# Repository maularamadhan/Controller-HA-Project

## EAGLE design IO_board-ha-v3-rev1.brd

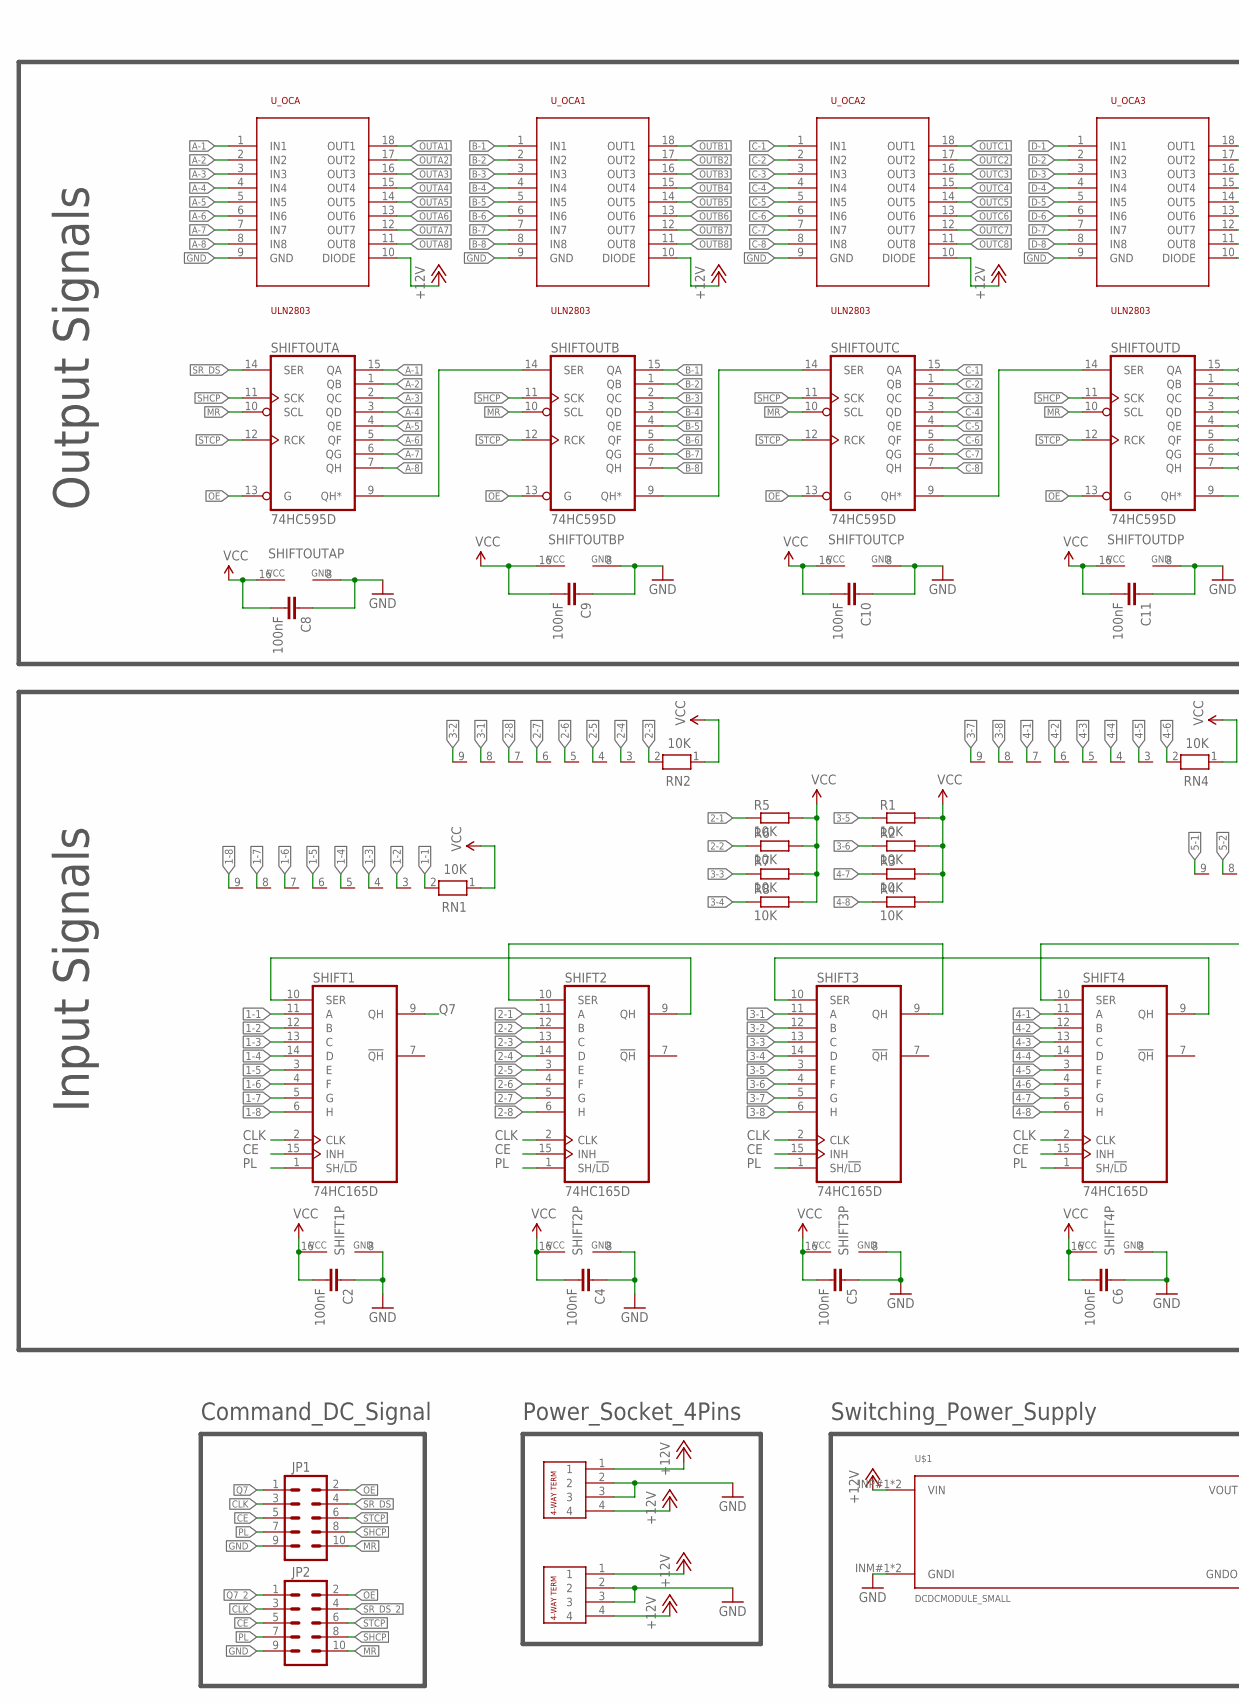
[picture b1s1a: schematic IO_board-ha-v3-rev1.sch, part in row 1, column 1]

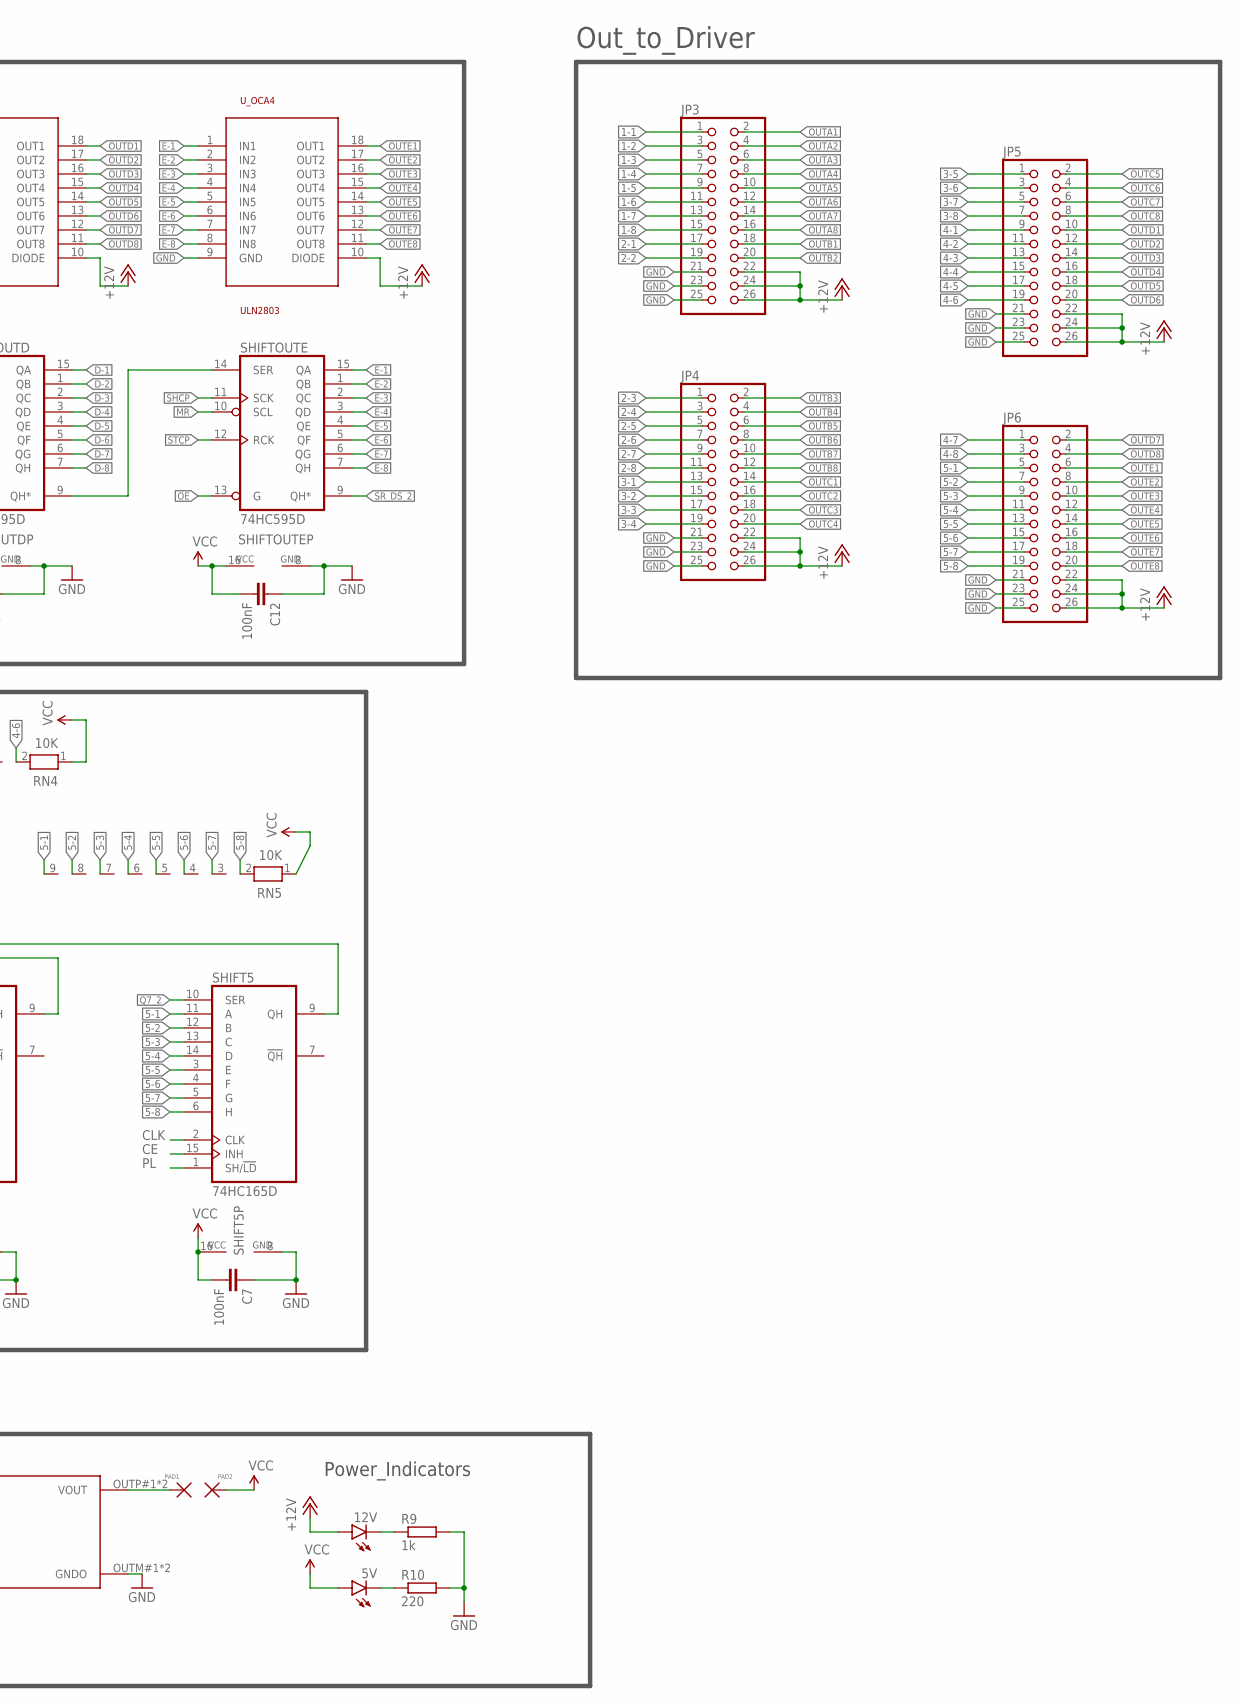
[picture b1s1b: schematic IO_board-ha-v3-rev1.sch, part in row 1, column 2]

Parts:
5V, 12V: LED3MM
C2, C4, C5, C6, C7, C8, C9, C10, C11, C12: 100nF; C0603K
J1, J2: 4-PIN-CON-1759017
JP1, JP2: M05X2SHD; 2X5-SHROUDED
JP3, JP4, JP5, JP6: PINHD-2X13; 2X13
R1, R2, R3, R4, R5, R6, R7, R8: 10K; R0603
R9: 1k; R0805
R10: 220; R0805
RN1, RN2, RN4, RN5: 10K; RN-9
SHIFT1, SHIFT2, SHIFT3, SHIFT4, SHIFT5: 74HC165D; SO16
SHIFTOUTA: 74HC595D; SO16
SHIFTOUTB: 74HC595D; SO16
SHIFTOUTC: 74HC595D; SO16
SHIFTOUTD: 74HC595D; SO16
SHIFTOUTE: 74HC595D; SO16
U$1: DCDCMODULE_SMALL; DCDCMODULE-SMALL
U$2: DOUBLE_SMALL_PAD
U_OCA, U_OCA1, U_OCA2, U_OCA3, U_OCA4: ULN2803; SO18L

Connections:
1-1: JP3.1, RN1.2, SHIFT1.11 (A)
1-2: JP3.3, RN1.3, SHIFT1.12 (B)
1-3: JP3.5, RN1.4, SHIFT1.13 (C)
1-4: JP3.7, RN1.5, SHIFT1.14 (D)
1-5: JP3.9, RN1.6, SHIFT1.3 (E)
1-6: JP3.11, RN1.7, SHIFT1.4 (F)
1-7: JP3.13, RN1.8, SHIFT1.5 (G)
1-8: JP3.15, RN1.9, SHIFT1.6 (H)
2-1: JP3.17, R5.1, SHIFT2.11 (A)
2-2: JP3.19, R6.1, SHIFT2.12 (B)
2-3: JP4.1, RN2.2, SHIFT2.13 (C)
2-4: JP4.3, RN2.3, SHIFT2.14 (D)
2-5: JP4.5, RN2.4, SHIFT2.3 (E)
2-6: JP4.7, RN2.5, SHIFT2.4 (F)
2-7: JP4.9, RN2.6, SHIFT2.5 (G)
2-8: JP4.11, RN2.7, SHIFT2.6 (H)
3-1: JP4.13, RN2.8, SHIFT3.11 (A)
3-2: JP4.15, RN2.9, SHIFT3.12 (B)
3-3: JP4.17, R7.1, SHIFT3.13 (C)
3-4: JP4.19, R8.1, SHIFT3.14 (D)
3-5: JP5.1, R1.1, SHIFT3.3 (E)
3-6: JP5.3, R2.1, SHIFT3.4 (F)
3-7: JP5.5, RN4.9, SHIFT3.5 (G)
3-8: JP5.7, RN4.8, SHIFT3.6 (H)
4-1: JP5.9, RN4.7, SHIFT4.11 (A)
4-2: JP5.11, RN4.6, SHIFT4.12 (B)
4-3: JP5.13, RN4.5, SHIFT4.13 (C)
4-4: JP5.15, RN4.4, SHIFT4.14 (D)
4-5: JP5.17, RN4.3, SHIFT4.3 (E)
4-6: JP5.19, RN4.2, SHIFT4.4 (F)
4-7: JP6.1, R3.1, SHIFT4.5 (G)
4-8: JP6.3, R4.1, SHIFT4.6 (H)
5-1: JP6.5, RN5.9, SHIFT5.11 (A)
5-2: JP6.7, RN5.8, SHIFT5.12 (B)
5-3: JP6.9, RN5.7, SHIFT5.13 (C)
5-4: JP6.11, RN5.6, SHIFT5.14 (D)
5-5: JP6.13, RN5.5, SHIFT5.3 (E)
5-6: JP6.15, RN5.4, SHIFT5.4 (F)
5-7: JP6.17, RN5.3, SHIFT5.5 (G)
5-8: JP6.19, RN5.2, SHIFT5.6 (H)
+12V: 12V.A, J1.1, J1.4, J2.1, J2.4, JP3.22, JP3.24, JP3.26, JP4.22, JP4.24, JP4.26, JP5.22, JP5.24, JP5.26, JP6.22, JP6.24, JP6.26, U$1.INP#1 (VIN), U$1.INP#2 (VIN), U_OCA.10 (DIODE), U_OCA1.10 (DIODE), U_OCA2.10 (DIODE), U_OCA3.10 (DIODE), U_OCA4.10 (DIODE)
A-1: SHIFTOUTA.15 (QA), U_OCA.1 (IN1)
A-2: SHIFTOUTA.1 (QB), U_OCA.2 (IN2)
A-3: SHIFTOUTA.2 (QC), U_OCA.3 (IN3)
A-4: SHIFTOUTA.3 (QD), U_OCA.4 (IN4)
A-5: SHIFTOUTA.4 (QE), U_OCA.5 (IN5)
A-6: SHIFTOUTA.5 (QF), U_OCA.6 (IN6)
A-7: SHIFTOUTA.6 (QG), U_OCA.7 (IN7)
A-8: SHIFTOUTA.7 (QH), U_OCA.8 (IN8)
B-1: SHIFTOUTB.15 (QA), U_OCA1.1 (IN1)
B-2: SHIFTOUTB.1 (QB), U_OCA1.2 (IN2)
B-3: SHIFTOUTB.2 (QC), U_OCA1.3 (IN3)
B-4: SHIFTOUTB.3 (QD), U_OCA1.4 (IN4)
B-5: SHIFTOUTB.4 (QE), U_OCA1.5 (IN5)
B-6: SHIFTOUTB.5 (QF), U_OCA1.6 (IN6)
B-7: SHIFTOUTB.6 (QG), U_OCA1.7 (IN7)
B-8: SHIFTOUTB.7 (QH), U_OCA1.8 (IN8)
C-1: SHIFTOUTC.15 (QA), U_OCA2.1 (IN1)
C-2: SHIFTOUTC.1 (QB), U_OCA2.2 (IN2)
C-3: SHIFTOUTC.2 (QC), U_OCA2.3 (IN3)
C-4: SHIFTOUTC.3 (QD), U_OCA2.4 (IN4)
C-5: SHIFTOUTC.4 (QE), U_OCA2.5 (IN5)
C-6: SHIFTOUTC.5 (QF), U_OCA2.6 (IN6)
C-7: SHIFTOUTC.6 (QG), U_OCA2.7 (IN7)
C-8: SHIFTOUTC.7 (QH), U_OCA2.8 (IN8)
CE: JP1.5, JP2.5, SHIFT1.15 (INH), SHIFT2.15 (INH), SHIFT3.15 (INH), SHIFT4.15 (INH), SHIFT5.15 (INH)
CLK: JP1.3, JP2.3, SHIFT1.2 (CLK), SHIFT2.2 (CLK), SHIFT3.2 (CLK), SHIFT4.2 (CLK), SHIFT5.2 (CLK)
D-1: SHIFTOUTD.15 (QA), U_OCA3.1 (IN1)
D-2: SHIFTOUTD.1 (QB), U_OCA3.2 (IN2)
D-3: SHIFTOUTD.2 (QC), U_OCA3.3 (IN3)
D-4: SHIFTOUTD.3 (QD), U_OCA3.4 (IN4)
D-5: SHIFTOUTD.4 (QE), U_OCA3.5 (IN5)
D-6: SHIFTOUTD.5 (QF), U_OCA3.6 (IN6)
D-7: SHIFTOUTD.6 (QG), U_OCA3.7 (IN7)
D-8: SHIFTOUTD.7 (QH), U_OCA3.8 (IN8)
E-1: SHIFTOUTE.15 (QA), U_OCA4.1 (IN1)
E-2: SHIFTOUTE.1 (QB), U_OCA4.2 (IN2)
E-3: SHIFTOUTE.2 (QC), U_OCA4.3 (IN3)
E-4: SHIFTOUTE.3 (QD), U_OCA4.4 (IN4)
E-5: SHIFTOUTE.4 (QE), U_OCA4.5 (IN5)
E-6: SHIFTOUTE.5 (QF), U_OCA4.6 (IN6)
E-7: SHIFTOUTE.6 (QG), U_OCA4.7 (IN7)
E-8: SHIFTOUTE.7 (QH), U_OCA4.8 (IN8)
GND: C2.1, C4.1, C5.1, C6.1, C7.1, C8.1, C9.1, C10.1, C11.1, C12.1, J1.2, J1.3, J2.2, J2.3, JP1.9, JP2.9, JP3.21, JP3.23, JP3.25, JP4.21, JP4.23, JP4.25, JP5.21, JP5.23, JP5.25, JP6.21, JP6.23, JP6.25, R9.2, R10.2, SHIFT1.8 (GND), SHIFT2.8 (GND), SHIFT3.8 (GND), SHIFT4.8 (GND), SHIFT5.8 (GND), SHIFTOUTA.8 (GND), SHIFTOUTB.8 (GND), SHIFTOUTC.8 (GND), SHIFTOUTD.8 (GND), SHIFTOUTE.8 (GND), U$1.INM#1 (GNDI), U$1.INM#2 (GNDI), U$1.OUTM#1 (GNDO), U$1.OUTM#2 (GNDO), U_OCA.9 (GND), U_OCA1.9 (GND), U_OCA2.9 (GND), U_OCA3.9 (GND), U_OCA4.9 (GND)
MR: JP1.10, JP2.10, SHIFTOUTA.10 (SCL), SHIFTOUTB.10 (SCL), SHIFTOUTC.10 (SCL), SHIFTOUTD.10 (SCL), SHIFTOUTE.10 (SCL)
unnamed: U$1.OUTP#1 (VOUT), U$1.OUTP#2 (VOUT), U$2.PAD1
unnamed: 12V.K (C), R9.1
unnamed: 5V.K (C), R10.1
unnamed: SHIFT2.10 (SER), SHIFT3.9 (QH)
unnamed: SHIFT3.10 (SER), SHIFT4.9 (QH)
unnamed: SHIFT4.10 (SER), SHIFT5.9 (QH)
unnamed: SHIFTOUTA.9 (QH*), SHIFTOUTB.14 (SER)
unnamed: SHIFTOUTC.9 (QH*), SHIFTOUTD.14 (SER)
unnamed: SHIFTOUTB.9 (QH*), SHIFTOUTC.14 (SER)
unnamed: SHIFTOUTD.9 (QH*), SHIFTOUTE.14 (SER)
unnamed: SHIFT1.10 (SER), SHIFT2.9 (QH)
OE: JP1.2, JP2.2, SHIFTOUTA.13 (G), SHIFTOUTB.13 (G), SHIFTOUTC.13 (G), SHIFTOUTD.13 (G), SHIFTOUTE.13 (G)
OUTA1: JP3.2, U_OCA.18 (OUT1)
OUTA2: JP3.4, U_OCA.17 (OUT2)
OUTA3: JP3.6, U_OCA.16 (OUT3)
OUTA4: JP3.8, U_OCA.15 (OUT4)
OUTA5: JP3.10, U_OCA.14 (OUT5)
OUTA6: JP3.12, U_OCA.13 (OUT6)
OUTA7: JP3.14, U_OCA.12 (OUT7)
OUTA8: JP3.16, U_OCA.11 (OUT8)
OUTB1: JP3.18, U_OCA1.18 (OUT1)
OUTB2: JP3.20, U_OCA1.17 (OUT2)
OUTB3: JP4.2, U_OCA1.16 (OUT3)
OUTB4: JP4.4, U_OCA1.15 (OUT4)
OUTB5: JP4.6, U_OCA1.14 (OUT5)
OUTB6: JP4.8, U_OCA1.13 (OUT6)
OUTB7: JP4.10, U_OCA1.12 (OUT7)
OUTB8: JP4.12, U_OCA1.11 (OUT8)
OUTC1: JP4.14, U_OCA2.18 (OUT1)
OUTC2: JP4.16, U_OCA2.17 (OUT2)
OUTC3: JP4.18, U_OCA2.16 (OUT3)
OUTC4: JP4.20, U_OCA2.15 (OUT4)
OUTC5: JP5.2, U_OCA2.14 (OUT5)
OUTC6: JP5.4, U_OCA2.13 (OUT6)
OUTC7: JP5.6, U_OCA2.12 (OUT7)
OUTC8: JP5.8, U_OCA2.11 (OUT8)
OUTD1: JP5.10, U_OCA3.18 (OUT1)
OUTD2: JP5.12, U_OCA3.17 (OUT2)
OUTD3: JP5.14, U_OCA3.16 (OUT3)
OUTD4: JP5.16, U_OCA3.15 (OUT4)
OUTD5: JP5.18, U_OCA3.14 (OUT5)
OUTD6: JP5.20, U_OCA3.13 (OUT6)
OUTD7: JP6.2, U_OCA3.12 (OUT7)
OUTD8: JP6.4, U_OCA3.11 (OUT8)
OUTE1: JP6.6, U_OCA4.18 (OUT1)
OUTE2: JP6.8, U_OCA4.17 (OUT2)
OUTE3: JP6.10, U_OCA4.16 (OUT3)
OUTE4: JP6.12, U_OCA4.15 (OUT4)
OUTE5: JP6.14, U_OCA4.14 (OUT5)
OUTE6: JP6.16, U_OCA4.13 (OUT6)
OUTE7: JP6.18, U_OCA4.12 (OUT7)
OUTE8: JP6.20, U_OCA4.11 (OUT8)
PL: JP1.7, JP2.7, SHIFT1.1 (SH/!LD), SHIFT2.1 (SH/!LD), SHIFT3.1 (SH/!LD), SHIFT4.1 (SH/!LD), SHIFT5.1 (SH/!LD)
Q7: JP1.1, SHIFT1.9 (QH)
Q7_2: JP2.1, SHIFT5.10 (SER)
SHCP: JP1.8, JP2.8, SHIFTOUTA.11 (SCK), SHIFTOUTB.11 (SCK), SHIFTOUTC.11 (SCK), SHIFTOUTD.11 (SCK), SHIFTOUTE.11 (SCK)
SR_DS: JP1.4, SHIFTOUTA.14 (SER)
SR_DS_2: JP2.4, SHIFTOUTE.9 (QH*)
STCP: JP1.6, JP2.6, SHIFTOUTA.12 (RCK), SHIFTOUTB.12 (RCK), SHIFTOUTC.12 (RCK), SHIFTOUTD.12 (RCK), SHIFTOUTE.12 (RCK)
VCC: 5V.A, C2.2, C4.2, C5.2, C6.2, C7.2, C8.2, C9.2, C10.2, C11.2, C12.2, R1.2, R2.2, R3.2, R4.2, R5.2, R6.2, R7.2, R8.2, RN1.1, RN2.1, RN4.1, RN5.1, SHIFT1.16 (VCC), SHIFT2.16 (VCC), SHIFT3.16 (VCC), SHIFT4.16 (VCC), SHIFT5.16 (VCC), SHIFTOUTA.16 (VCC), SHIFTOUTB.16 (VCC), SHIFTOUTC.16 (VCC), SHIFTOUTD.16 (VCC), SHIFTOUTE.16 (VCC), U$2.PAD2

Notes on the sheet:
Input Signals
Output Signals
Out_to_Driver
Command_DC_Signal
Power_Socket_4Pins
Switching_Power_Supply
Power_Indicators

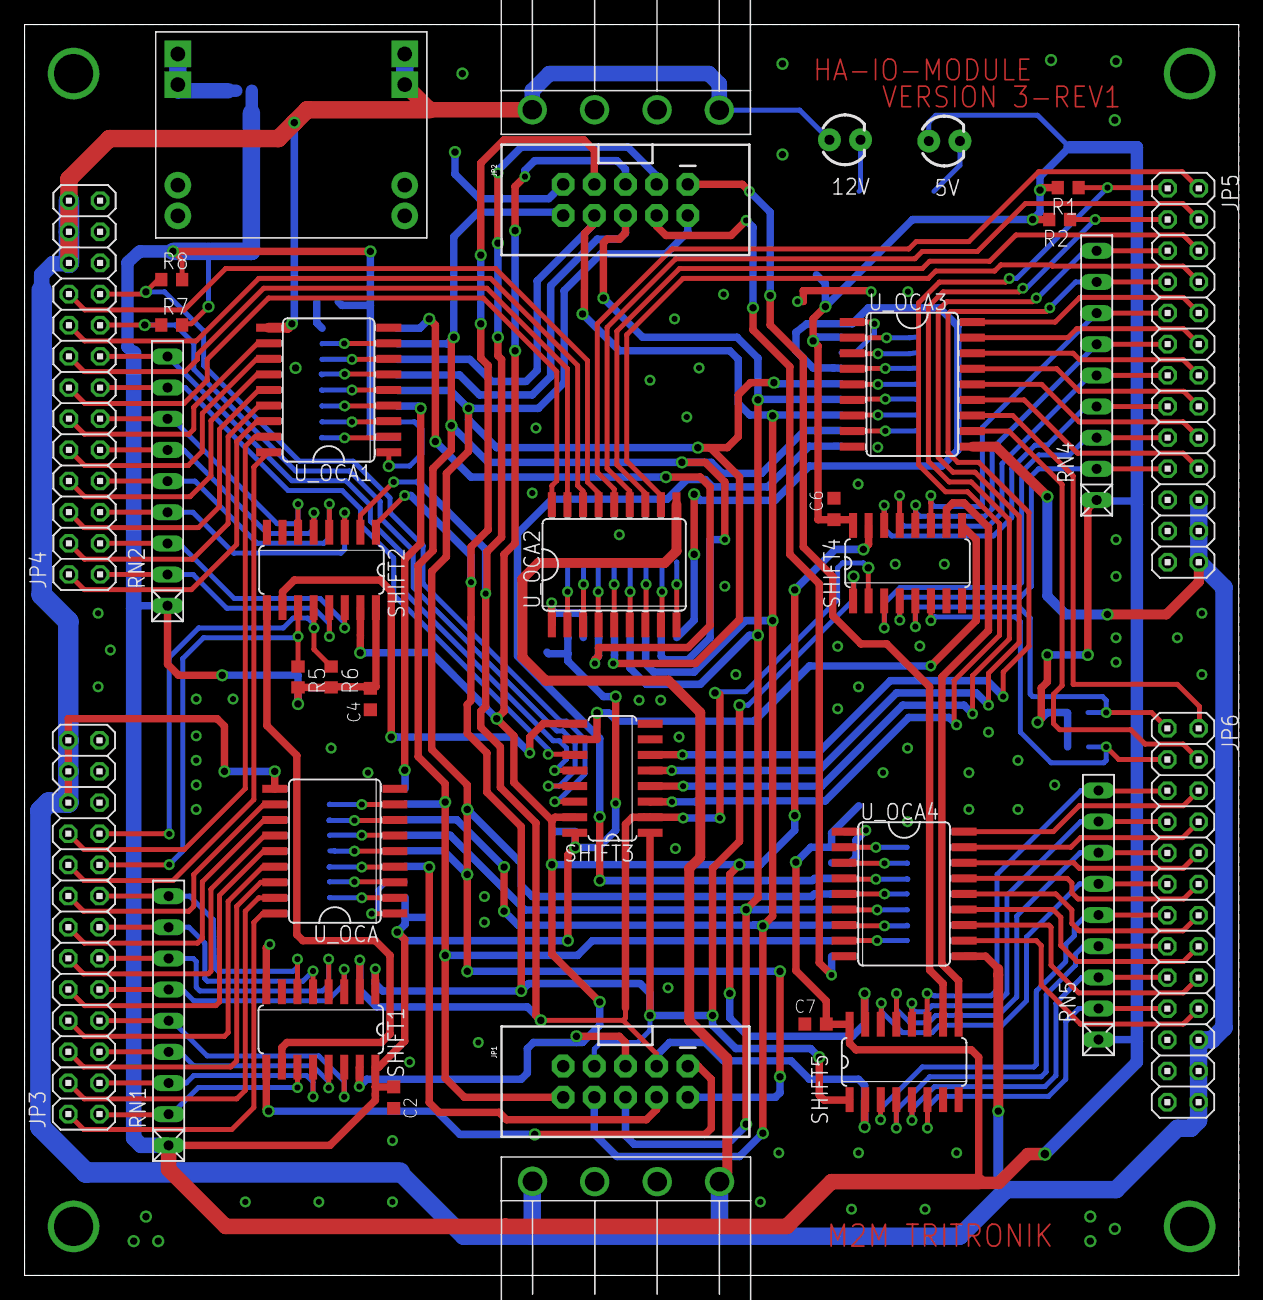
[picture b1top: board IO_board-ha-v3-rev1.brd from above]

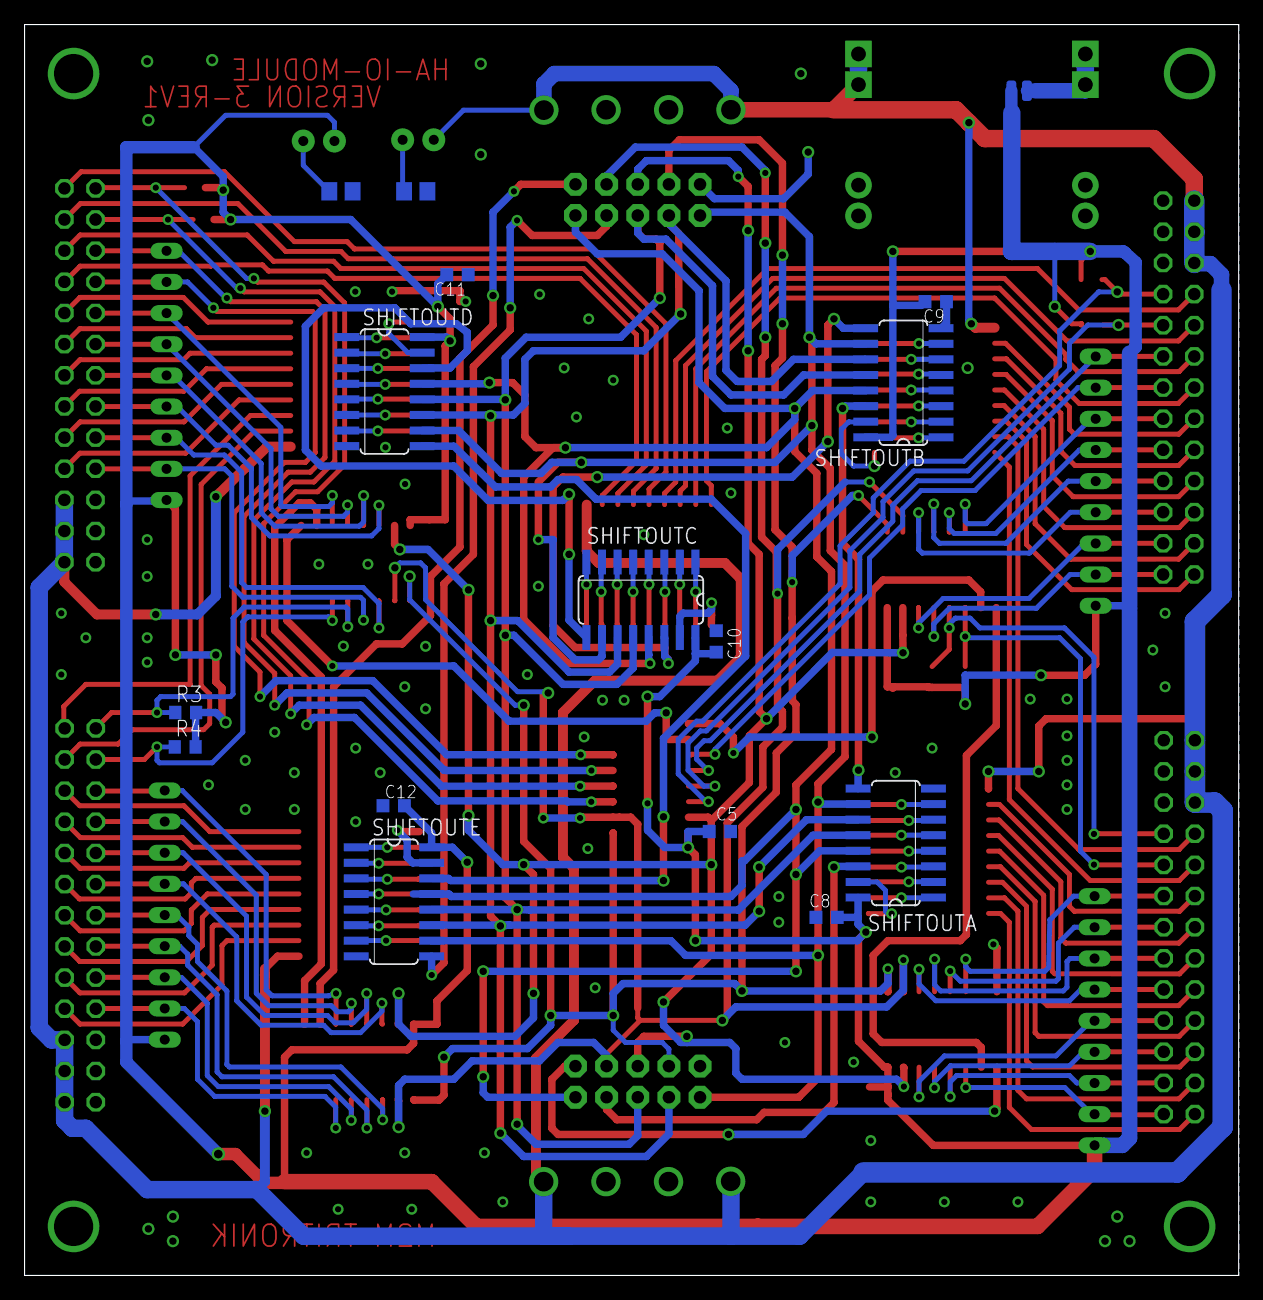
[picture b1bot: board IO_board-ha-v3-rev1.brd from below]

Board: 2 copper layers, 99.0 x 102.0 mm, 51 parts (16 on the bottom side), 145 nets.

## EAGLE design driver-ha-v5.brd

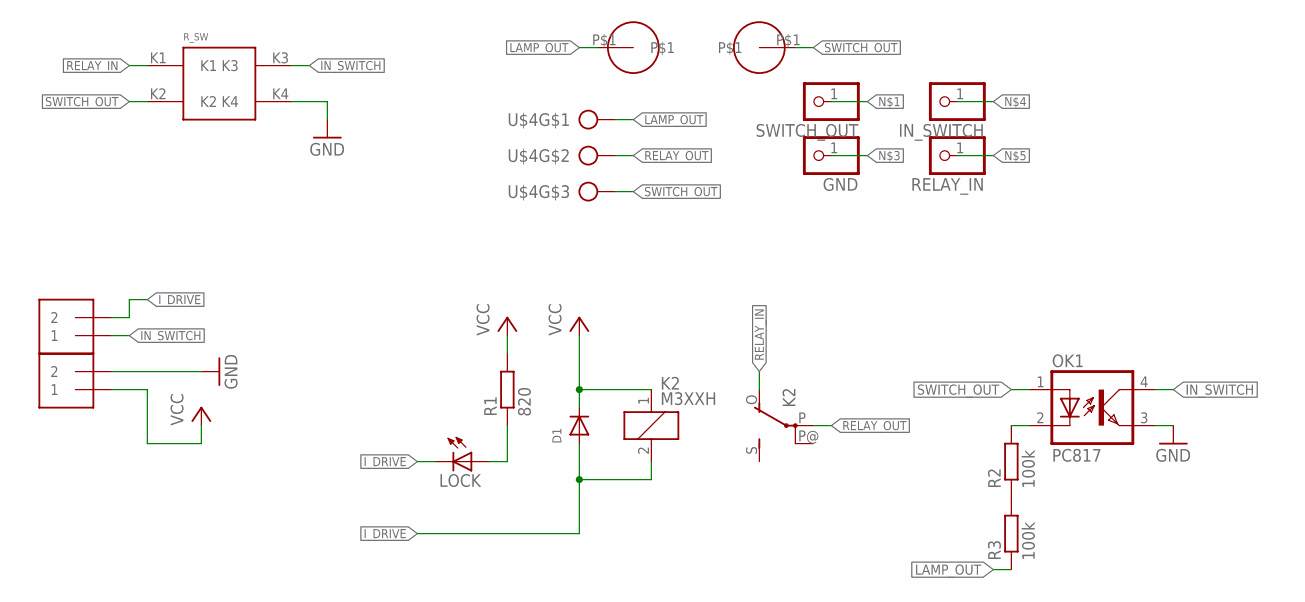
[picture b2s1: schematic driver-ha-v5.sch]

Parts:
D1: DIODESMA; SMADIODE
GND: PINHD-1X1; 1X01
IN_SWITCH: PINHD-1X1; 1X01
J1, J2: 1X2-3.5MM
K2: M3XXH
LOCK: LED3MM
OK1: PC817; DIL04
PAD1: ROOM_SWITCH
R1: 820; R0805
R2, R3: 100k; R1206
RELAY_IN: PINHD-1X1; 1X01
SWITCH_OUT: PINHD-1X1; 1X01
U$1, U$3: CONN-CABLE
U$4: AK3003

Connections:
GND: J2.2, OK1.3 (EMIT), PAD1.K4
IN_SWITCH: J1.1, OK1.4 (COL), PAD1.K3
I_DRIVE: D1.A, J1.2, K2.2, LOCK.K (C)
LAMP_OUT: R3.1, U$1.P$1, U$4.1
unnamed: LOCK.A, R1.1
unnamed: R2.1, R3.2
unnamed: OK1.2 (C), R2.2
RELAY_IN: K2.O, PAD1.K1
RELAY_OUT: K2.P, U$4.2
SWITCH_OUT: OK1.1 (A), PAD1.K2, U$3.P$1, U$4.3
VCC: D1.C, J2.1, K2.1, R1.2

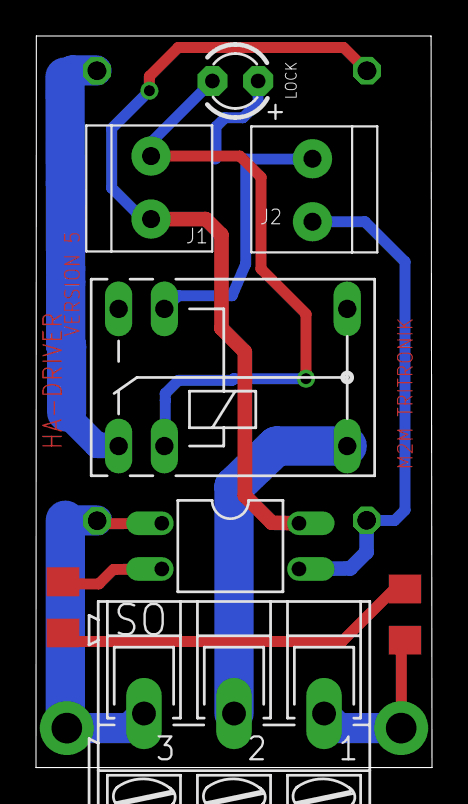
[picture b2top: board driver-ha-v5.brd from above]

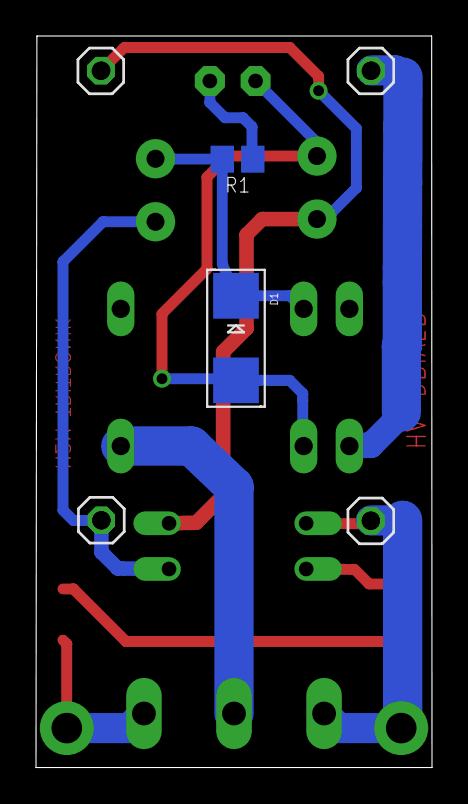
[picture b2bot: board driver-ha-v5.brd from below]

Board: 2 copper layers, 22.0 x 40.6 mm, 17 parts (6 on the bottom side), 11 nets.

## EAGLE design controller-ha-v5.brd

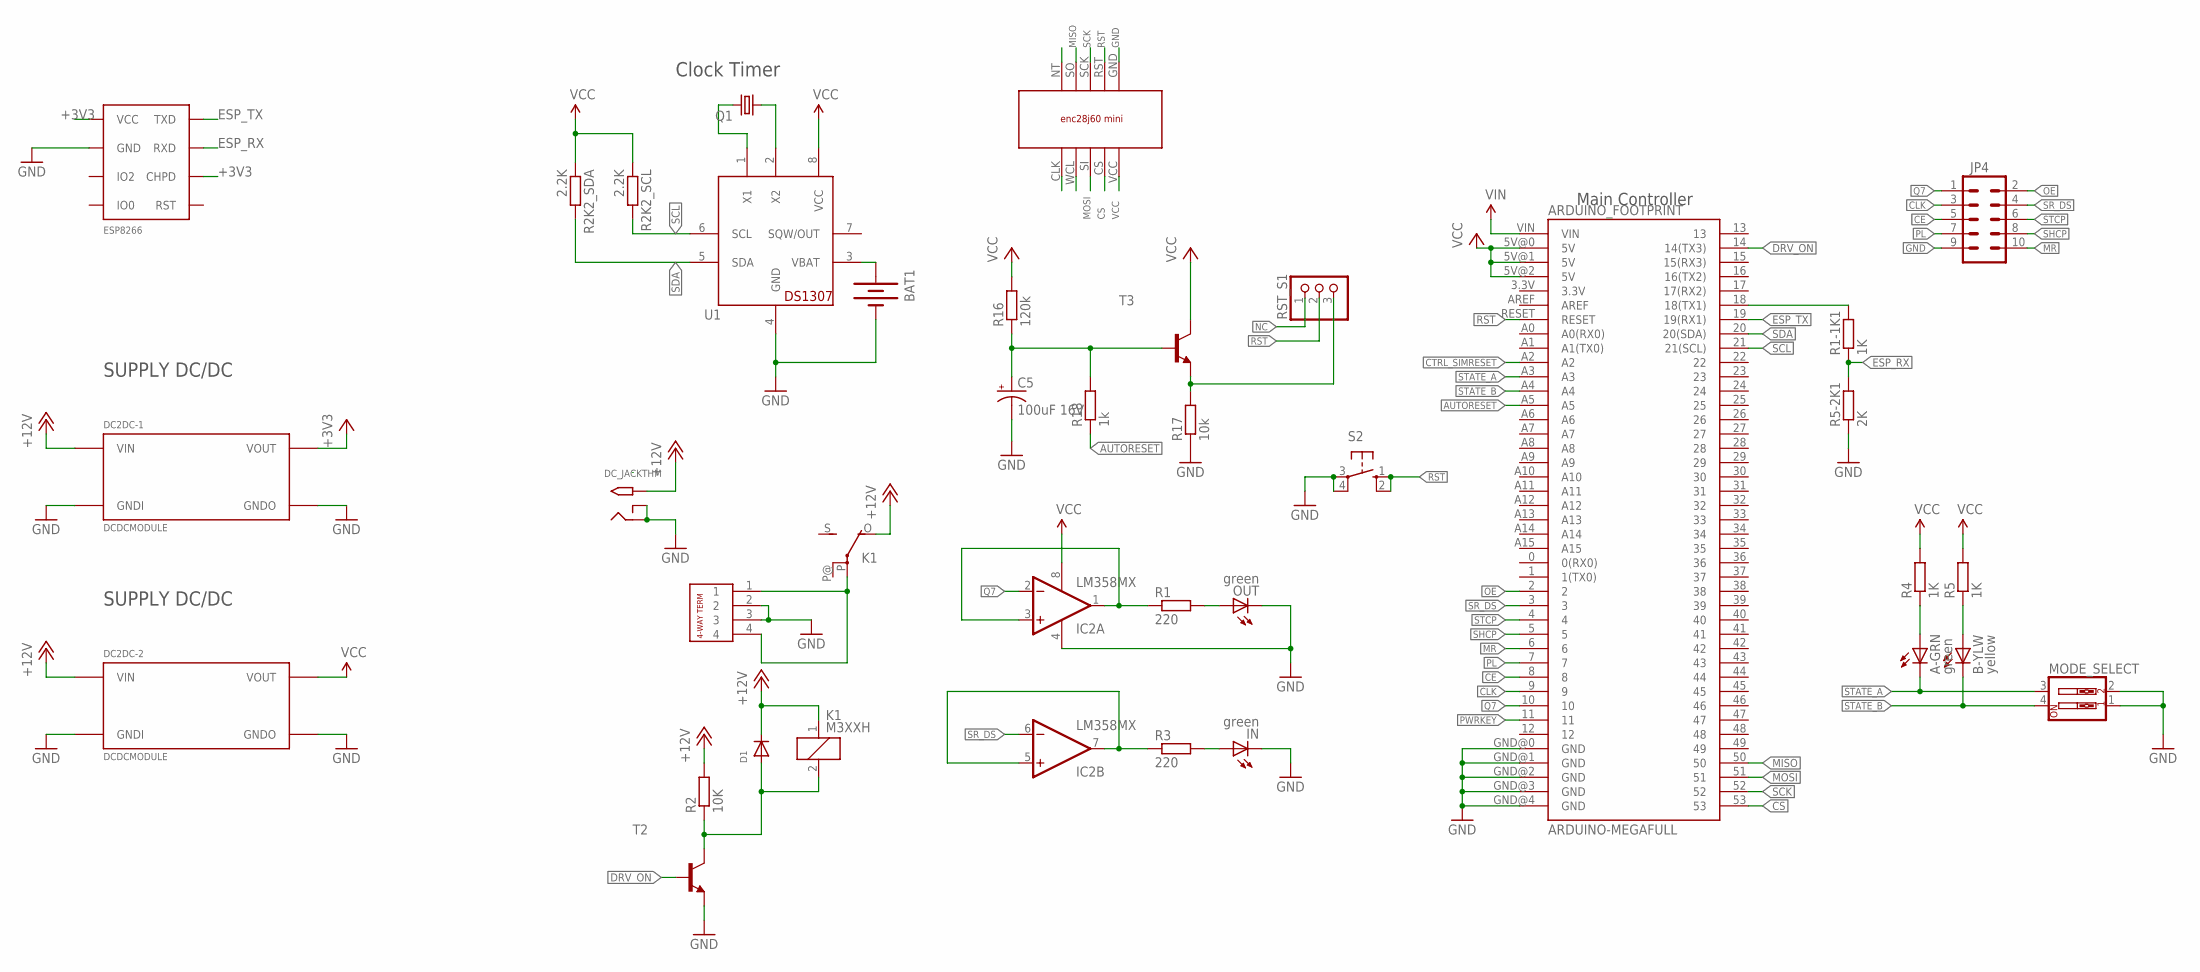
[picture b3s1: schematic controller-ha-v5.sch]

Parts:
4-WAY_L-TERMINAL: 4-PIN-CON-1759017
A-GRN: green; CHIP-LED0805
ARDUINO_FOOTPRINT: ARDUINO-MEGAFULL; ARDUINO_MEGA
B-YLW: yellow; CHIP-LED0805
BAT1: BATTERY20PTH; BATTCOM_20MM_PTH
C5: 100uF 16V; 153CLV-0605
D1: DIODESMA; SMADIODE
DC2DC-1, DC2DC-2: DCDCMODULE
DC_JACKTHM: 2.1MMJACKTHM; PJ-102A
ESP8266: ESP8266
IC2: LM358MX; SO08
IN: green; CHIPLED_0805
JP4: M05X2RA; 2X5-RA
K1: M3XXH
MODE_SELECT: SW_DIP-2; EDG-02
OUT: green; CHIPLED_0805
Q1: CRYSTALTC26H; TC26H
R1, R3: 220; R0805
R1-1K1: 1K; R0603
R2: 10K; R0805
R2K2_SCL, R2K2_SDA: 2.2K; R0603
R4, R5: 1K; R0805
R5-2K1: 2K; R0603
R16: 120k; R0805
R17: 10k; R0805
R18: 1k; R0805
RST_S1: PINHD-1X3CB; 1X03-CLEANBIG
S2: 10-XX; B3F-10XX
T2, T3: MMBT2222ALT1-NPN-SOT23-BEC; SOT23-BEC
U1: DS1307; DIL08
U$2: ENC28J60_MODULE_BOTTOM

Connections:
+3V3: DC2DC-1.VOUT, ESP8266.CHPD, ESP8266.VCC
+12V: D1.C, DC2DC-1.VIN, DC2DC-2.VIN, DC_JACKTHM.TIP, K1.1, K1.O, R2.2
AUTORESET: ARDUINO_FOOTPRINT.A5, R18.1
CE: ARDUINO_FOOTPRINT.8, JP4.5
CLK: ARDUINO_FOOTPRINT.9, JP4.3
CS: ARDUINO_FOOTPRINT.53, U$2.CS
CTRL_SIMRESET: ARDUINO_FOOTPRINT.A2
DRV_ON: ARDUINO_FOOTPRINT.14 (14(TX3)), T2.B
ESP_RX: ESP8266.RXD, R1-1K1.1, R5-2K1.2
ESP_TX: ARDUINO_FOOTPRINT.19 (19(RX1)), ESP8266.TXD
GND: 4-WAY_L-TERMINAL.2, 4-WAY_L-TERMINAL.3, ARDUINO_FOOTPRINT.GND@0 (GND), ARDUINO_FOOTPRINT.GND@1 (GND), ARDUINO_FOOTPRINT.GND@2 (GND), ARDUINO_FOOTPRINT.GND@3 (GND), ARDUINO_FOOTPRINT.GND@4 (GND), BAT1.2 (-), C5.-, DC2DC-1.GND#0 (GNDI), DC2DC-1.GND#1 (GNDO), DC2DC-2.GND#0 (GNDI), DC2DC-2.GND#1 (GNDO), DC_JACKTHM.RING, DC_JACKTHM.RING_SW, ESP8266.GND, IC2.4 (V-), IN.C, JP4.9, MODE_SELECT.1, MODE_SELECT.2, OUT.C, R5-2K1.1, R17.1, S2.3, S2.4 (P1), T2.E, U1.4 (GND), U$2.GND
MISO: ARDUINO_FOOTPRINT.50, U$2.SO
MOSI: ARDUINO_FOOTPRINT.51, U$2.SI
MR: ARDUINO_FOOTPRINT.6, JP4.10
unnamed: 4-WAY_L-TERMINAL.1, 4-WAY_L-TERMINAL.4, K1.P
unnamed: D1.A, K1.2, R2.1, T2.C
unnamed: R17.2, RST_S1.3, T3.E
unnamed: Q1.1, U1.2 (X2)
unnamed: Q1.2, U1.1 (X1)
unnamed: ARDUINO_FOOTPRINT.18 (18(TX1)), R1-1K1.2
unnamed: IC2.1 (OUT), IC2.3 (+IN), R1.1
unnamed: BAT1.1 (+), U1.3 (VBAT)
unnamed: IC2.5 (+IN), IC2.7 (OUT), R3.1
unnamed: OUT.A, R1.2
unnamed: IN.A, R3.2
unnamed: A-GRN.A, R4.1
unnamed: B-YLW.A, R5.1
NC: RST_S1.1
NET1: C5.+, R16.1, R18.2, T3.B
OE: ARDUINO_FOOTPRINT.2, JP4.2
PL: ARDUINO_FOOTPRINT.7, JP4.7
PWRKEY: ARDUINO_FOOTPRINT.11
Q7: ARDUINO_FOOTPRINT.10, IC2.2 (-IN), JP4.1
RST: ARDUINO_FOOTPRINT.RESET, RST_S1.2, S2.1 (S), S2.2 (S1), U$2.RST
SCK: ARDUINO_FOOTPRINT.52, U$2.SCK
SCL: ARDUINO_FOOTPRINT.21 (21(SCL)), R2K2_SCL.2, U1.6 (SCL)
SDA: ARDUINO_FOOTPRINT.20 (20(SDA)), R2K2_SDA.2, U1.5 (SDA)
SHCP: ARDUINO_FOOTPRINT.5, JP4.8
SR_DS: ARDUINO_FOOTPRINT.3, IC2.6 (-IN), JP4.4
STATE_A: A-GRN.C, ARDUINO_FOOTPRINT.A3, MODE_SELECT.3
STATE_B: ARDUINO_FOOTPRINT.A4, B-YLW.C, MODE_SELECT.4
STCP: ARDUINO_FOOTPRINT.4, JP4.6
VCC: ARDUINO_FOOTPRINT.5V@0 (5V), ARDUINO_FOOTPRINT.5V@1 (5V), ARDUINO_FOOTPRINT.5V@2 (5V), DC2DC-2.VOUT, IC2.8 (V+), R2K2_SCL.1, R2K2_SDA.1, R4.2, R5.2, R16.2, T3.C, U1.8 (VCC), U$2.VCC
VIN: ARDUINO_FOOTPRINT.VIN

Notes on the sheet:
Clock Timer
Main Controller
SUPPLY DC/DC

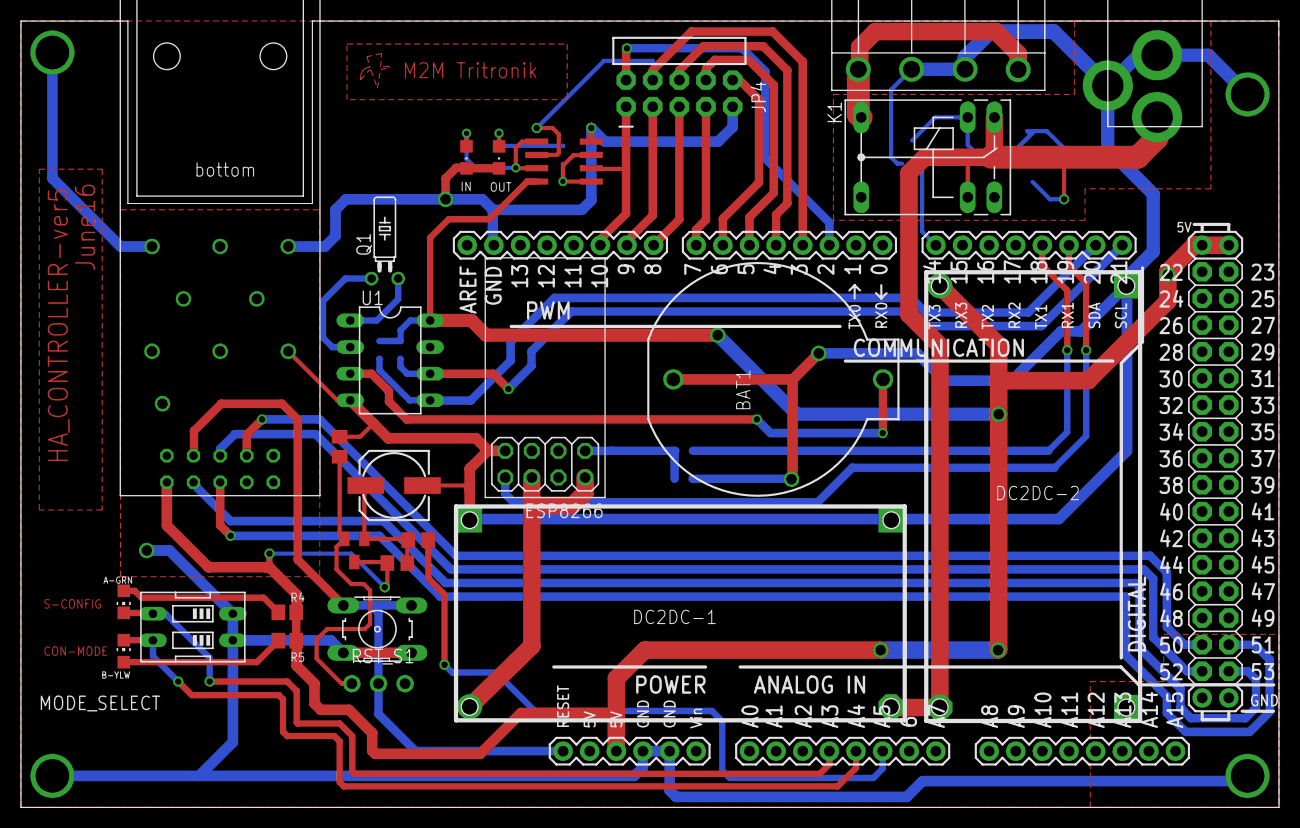
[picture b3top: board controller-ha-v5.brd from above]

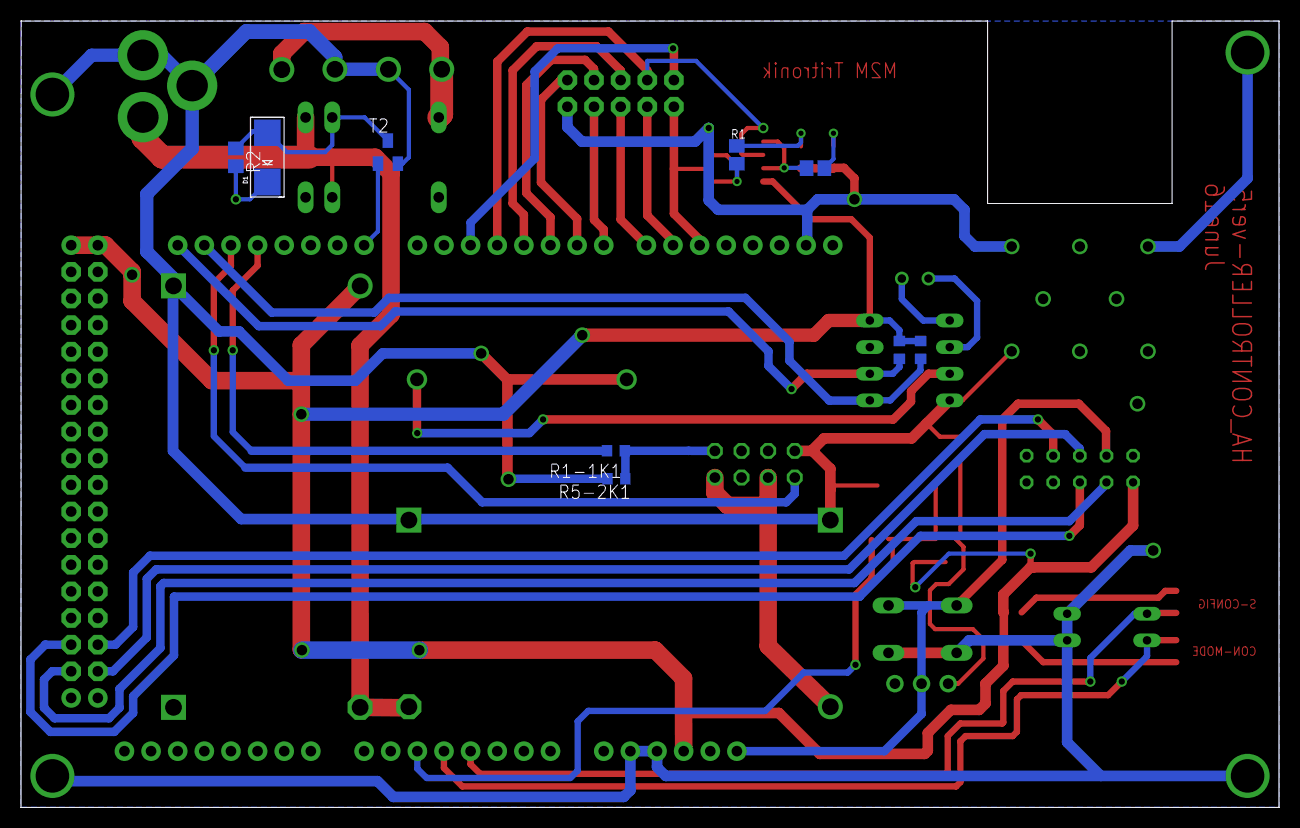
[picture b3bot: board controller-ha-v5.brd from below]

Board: 2 copper layers, 120.0 x 75.0 mm, 36 parts (9 on the bottom side), 40 nets.

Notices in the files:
parts and their libraries:
SparkFun-Connectors: Licensing: Creative Commons ShareAlike 4.0 International - https://creativecommons.org/licenses/by-sa/4.0
SparkFun: Licensing: CC v3.0 Share-Alike You are welcome to use this library for commercial purposes.
